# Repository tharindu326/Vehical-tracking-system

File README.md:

# Vehical-tracking-system

System will detect vehicle’s movements using the vibrations of vehicle and then notify the owner in any case of unidentified movements.

Here I used Peizo to identify vibrations using amplified voltage variations, GPS module (Ublox neo-6m) to identify the coordinates of the location and then GSM (SIM800) module to transmit the data to the mobile device.

And used a mobile application (Android) to request the real time location of the vehicle at any time. And initiation of the phone number and activation can be done using the app as well as it also allows the owner to turn on and off the system at any time.

Arduino UNO was used as the microcontroller and Android studio was used to program the application. Buck converter is used to power up the GPS and GSM modules since its slightly power hungry. Vehicle GPS antenna was used to achieve  more reliable signal strength.

Open Source Licence

Feel free to use this codes and let me know your comments.

[Author] Tharindu Ekanayake _ tharindu326@gmail.com

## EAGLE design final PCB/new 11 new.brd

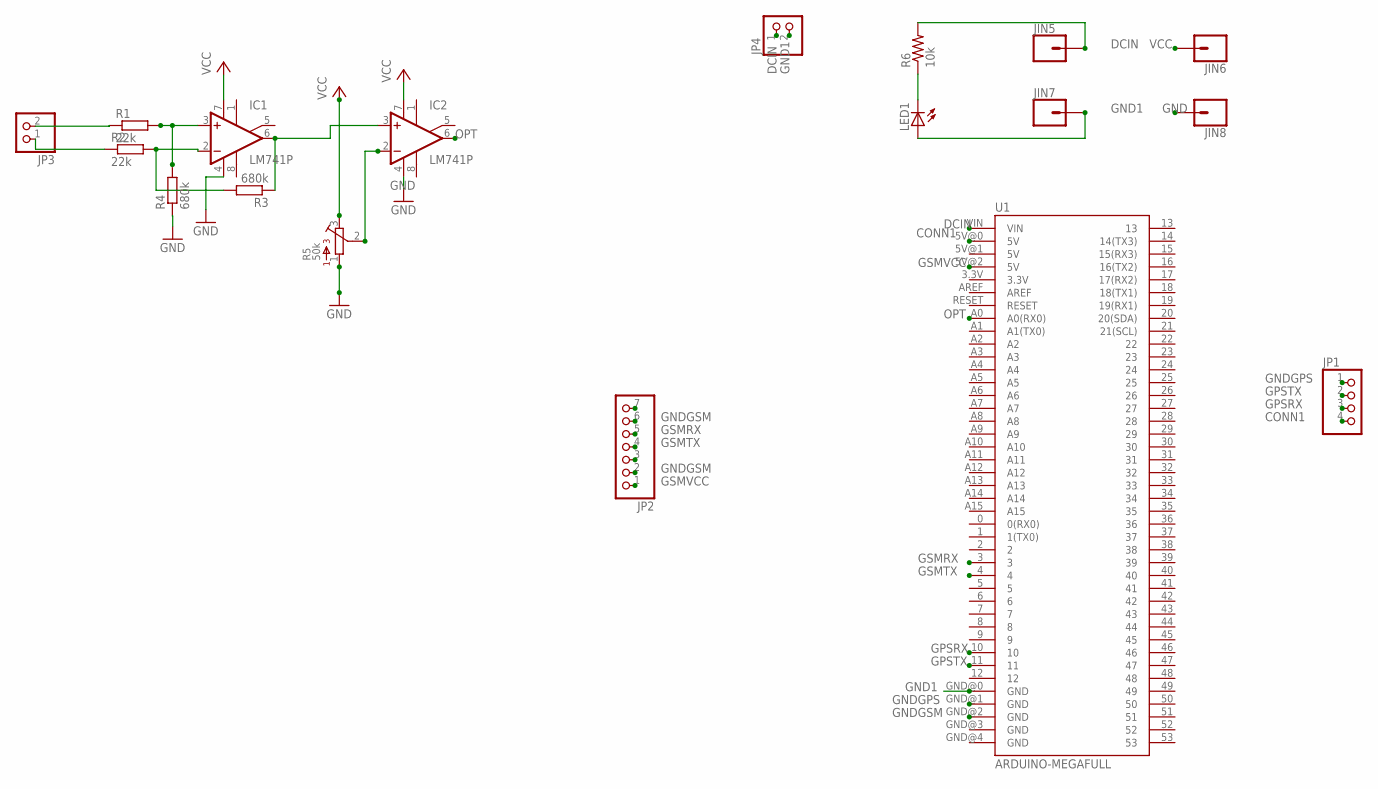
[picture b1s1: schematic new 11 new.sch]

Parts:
IC1, IC2: LM741P; DIL08
JIN5, JIN6, JIN7, JIN8: CONN_01; 1X01
JP1: PINHD-1X4; 1X04
JP2: PINHD-1X7; 1X07
JP3, JP4: PINHD-1X2; 1X02
LED1: LEDSQR2X5; LED2X5
R1, R2: 22k; 0204/7
R3, R4: 680k; 0204/7
R5: 50k; 3362H
R6: 10k; 0204/5
U1: ARDUINO-MEGAFULL; ARDUINO_MEGA

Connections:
CONN1: JP1.4, U1.5V@0 (5V)
DCIN: JIN5.1, JP4.1, R6.2, U1.VIN
GND: IC1.4 (V-), IC2.4 (V-), JIN8.1, R4.1, R5.1
GND1: JIN7.1, JP4.2, LED1.A, U1.GND@0 (GND)
GNDGPS: JP1.1, U1.GND@1 (GND)
GNDGSM: JP2.2, JP2.6, U1.GND@2 (GND)
GPSRX: JP1.3, U1.10
GPSTX: JP1.2, U1.11
GSMRX: JP2.5, U1.3
GSMTX: JP2.4, U1.4
GSMVCC: JP2.1, U1.5V@2 (5V)
unnamed: IC1.6 (OUT), IC2.3 (+IN), R3.1
unnamed: IC1.2 (-IN), R2.2, R3.2
unnamed: JP3.1, R2.1
unnamed: LED1.K (C), R6.1
unnamed: JP3.2, R1.1
unnamed: IC2.2 (-IN), R5.2
unnamed: IC1.3 (+IN), R1.2, R4.2
OPT: IC2.6 (OUT), U1.A0 (A0(RX0))
VCC: IC1.7 (V+), IC2.7 (V+), JIN6.1, R5.3

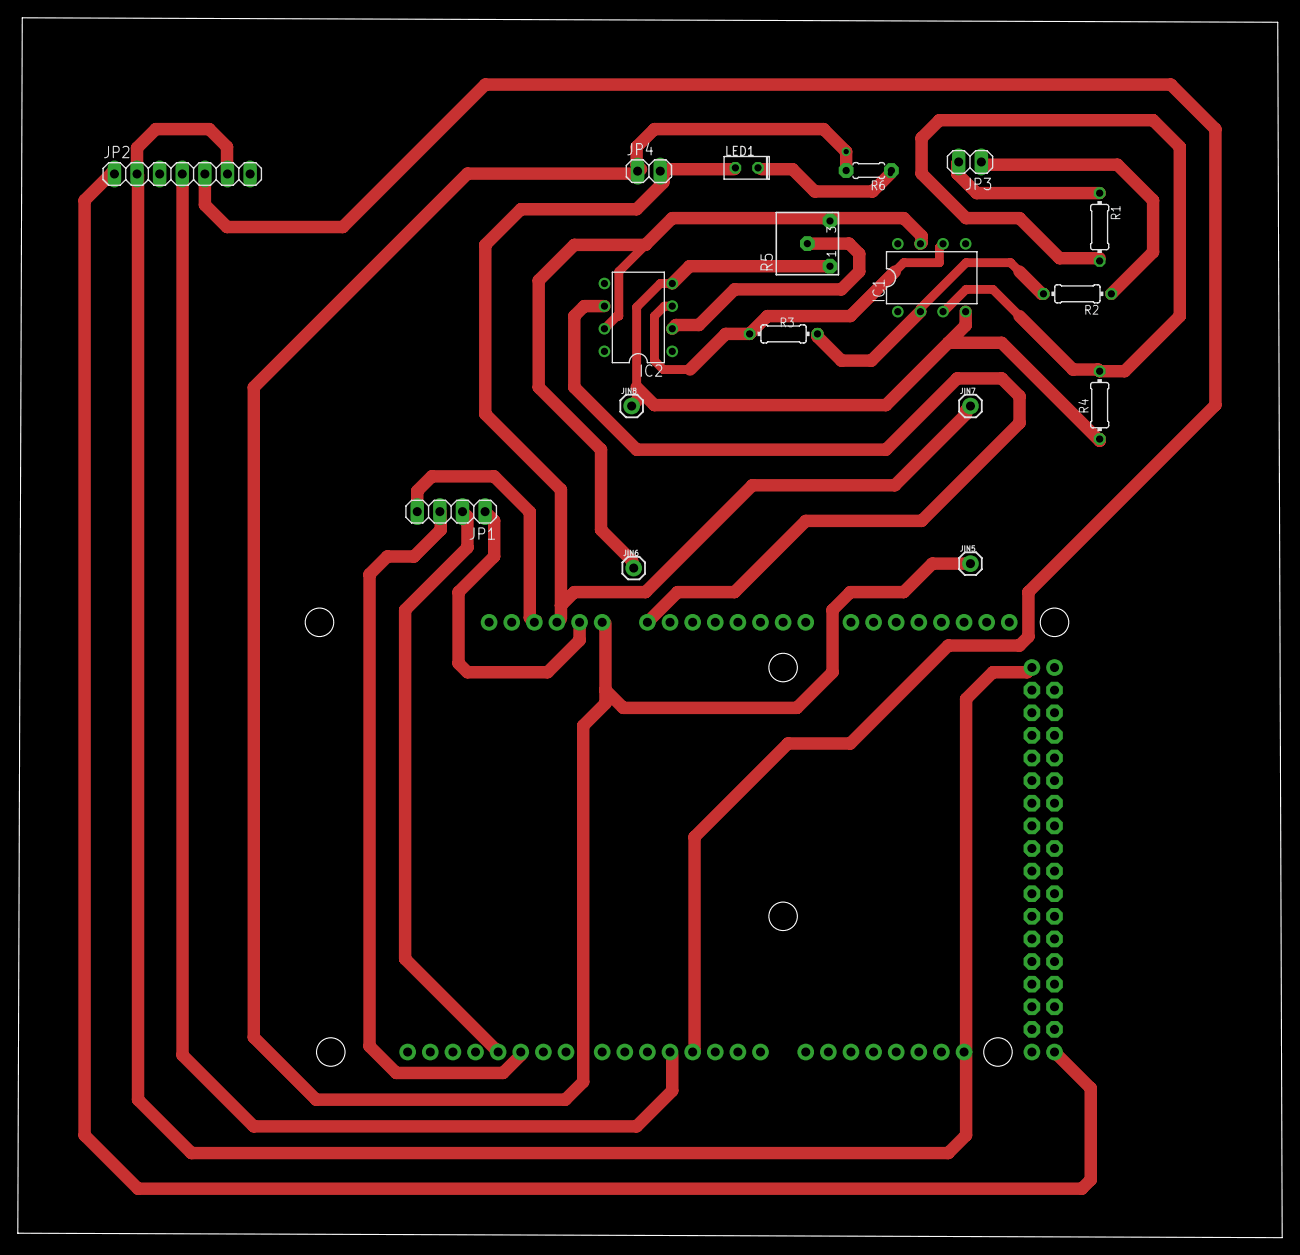
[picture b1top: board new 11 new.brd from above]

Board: 2 copper layers, 142.0 x 137.0 mm, 18 parts (1 on the bottom side), 20 nets.

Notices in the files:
parts and their libraries:
SparkFun-Connectors: Licensing: Creative Commons ShareAlike 4.0 International - https://creativecommons.org/licenses/by-sa/4.0
